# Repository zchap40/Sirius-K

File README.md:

# Sirius-K
Transparent overdrive guitar effects pedal

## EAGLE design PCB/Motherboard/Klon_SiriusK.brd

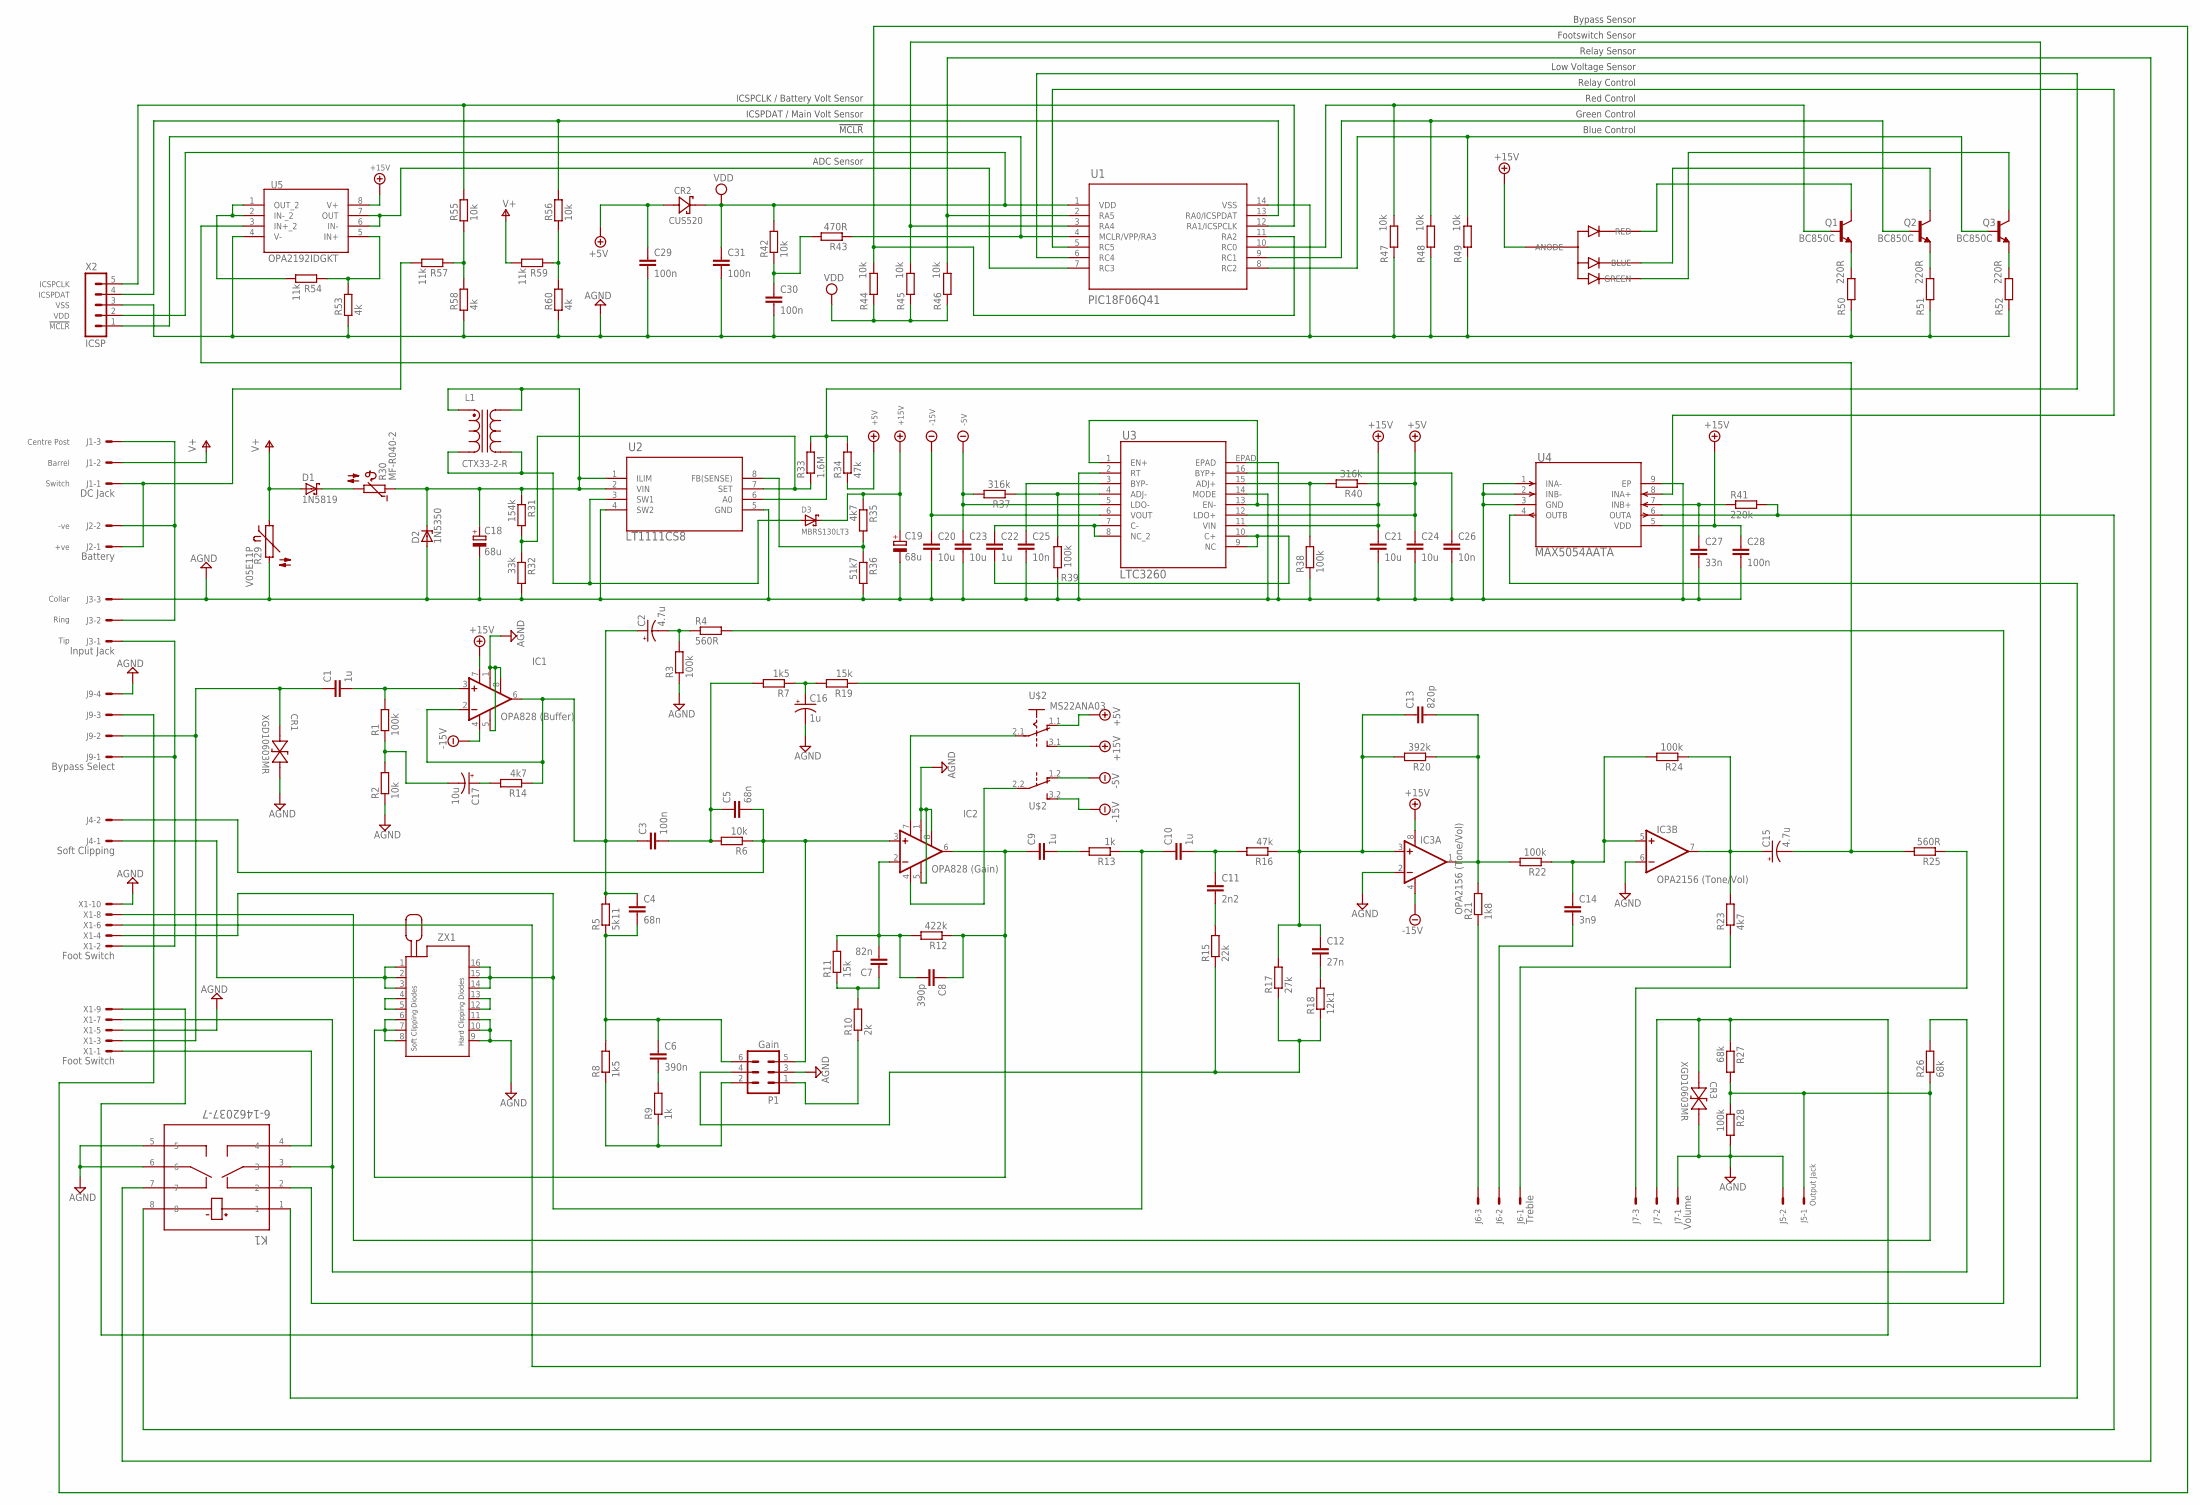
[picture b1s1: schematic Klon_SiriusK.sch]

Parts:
C1, C9, C10: 1u; C225-108X268
C2, C15: 4.7u; E15-5
C3: 100n; C102-064X133
C4, C5: 68n; C102-054X133
C6: 390n; C102-064X133
C7: 82n; C102-064X133
C8: 390p; C050-045X075
C11: 2n2; C075-042X103
C12: 27n; C102-064X133
C13: 820p; C050-050X075
C14: 3n9; C102-064X133
C16: 1u; E2,5RE
C17: 10u; E5R
C18, C19: 68u; SANYO-OSCON_SMD_F12
C20, C21, C23, C24: 10u; C1206K
C22: 1u; C0805K
C25, C26: 10n; C0603K
C27: 33n; C0603K
C28, C29, C30, C31: 100n; C0603K
CR1, CR3: XGD10603MR; ZDO_XGD10603NR_LTF-M
CR2: CUS520; USC_TOS-M
D1: 1N5819; DO41-7.6
D2: 1N5350; C1702-15
D3: MBRS130LT3; SMB
IC1: OPA828 (Buffer); DIL08
IC2: OPA828 (Gain); DIL08
IC3: OPA2156 (Tone/Vol); DIL08
J1: DC Jack; 6410-03
J2: Battery; 6410-02
J3: Input Jack; 6410-03
J4: Soft Clipping; 6410-02
J5: Output Jack; 6410-02
J6: Treble; 6410-03
J7: Volume; 6410-03
J9: Bypass Select; 6410-04
K1: 6-1462037-7; RELAY8_SMTGUL_TEC
L1: CTX33-2-R; INDM889889X597N
LED: WP154A4SEJ3VBDZGW/CA; LED5MMRGB
P1: Gain; 87831-06
Q1, Q2, Q3: BC850C; SOT23-BEC
R1, R3, R22, R24, R28: 100k; 0309/12
R2, R6: 10k; 0309/12
R4, R25: 560R; 0309/12
R5: 5k11; 0309/12
R7, R8: 1k5; 0309/12
R9, R13: 1k; 0309/12
R10: 2k; 0309/12
R11, R19: 15k; 0309/12
R12: 422k; 0309/12
R14, R23: 4k7; 0309/12
R15: 22k; 0309/12
R16: 47k; 0309/12
R17: 27k; 0309/12
R18: 12k1; 0309/12
R20: 392k; 0309/12
R21: 1k8; 0309/12
R26, R27: 68k; 0309/12
R29: V05E11P; S05K11
R30: MF-R040-2; B57164
R31: 154k; R0603
R32: 33k; R0603
R33: 1.6M; R0603
R34: 47k; R0603
R35: 4k7; R0603
R36: 51k7; R0603
R37, R40: 316k; R0603
R38, R39: 100k; R0603
R41: 220k; R0603
R42, R44, R45, R46, R47, R48, R49, R55, R56: 10k; R0603
R43: 470R; R0603
R50, R51, R52: 220R; R0603
R53, R58, R60: 4k; R0603
R54, R57, R59: 11k; R0603
U1: PIC18F06Q41; TSSOP14_ST_MCH-M
U2: LT1111CS8; SO-8_S_LIT-M
U3: LTC3260; MSOP-16_MSE_LIT-M
U4: MAX5054AATA; 21-0137_T833+2_MXM-M
U5: OPA2192IDGKT; DGK0008A_N_TEX
U$2: MS22ANA03
X1: Foot Switch; 87758-1016
X2: ICSP; MA05-1
ZX1: 216-3340-00-0602J

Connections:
+5V: C24.1, C29.1, CR2.2 (ANODE), R34.1, R40.1, U3.12 (LDO+), U$2.1.1 (O)
+15V: C19.+, C21.1, C28.1, D3.C, IC1.7 (V+), IC3.8 (V+), LED.P2 (ANODE), R35.1, U3.1 (EN+), U3.11 (VIN), U3.13 (EN-), U4.5 (VDD), U5.8 (V+), U$2.3.1 (S)
-5V: C23.1, R37.2, U3.5 (LDO-), U$2.1.2 (O)
-15V: C20.1, IC1.4 (V-), IC3.4 (V-), U3.6 (VOUT), U$2.3.2 (S)
AGND: C16.-, C18.-, C19.-, C20.2, C21.2, C23.2, C24.2, C25.2, C26.2, C27.2, C28.2, C29.2, C30.2, C31.2, CR1.1 (11), CR3.1 (11), D2.A, IC1.1 (TRIM1), IC1.5 (TRIM2), IC1.8 (NC), IC2.1 (TRIM1), IC2.5 (TRIM2), IC2.8 (NC), IC3.2 (-IN), IC3.6 (-IN), J3.3, J5.2, J7.1, J9.4, K1.5, K1.6, P1.3, R2.1, R3.1, R28.2, R29.2, R32.2, R36.2, R38.1, R39.1, R47.1, R48.1, R49.1, R50.1, R51.1, R52.1, R53.1, R58.1, R60.1, U1.14 (VSS), U2.4 (SW2), U2.5 (GND), U3.2 (RT), U3.14 (MODE), U3.EPAD, U4.1 (INA-), U4.2 (INB-), U4.3 (GND), U4.9 (EP), U5.4 (V-), X1.5, X1.10, X2.3, ZX1.9, ZX1.10, ZX1.11
unnamed: J1.1, J2.1, R57.2
unnamed: J1.3, J2.2, J3.2
unnamed: C1.1, CR1.2 (12), J9.2, X1.3
unnamed: C1.2, IC1.3 (+IN), R1.2
unnamed: C17.-, R1.1, R2.2
unnamed: C2.+, C3.1, C4.1, IC1.2 (-IN), IC1.6 (OUT), R5.2, R14.1
unnamed: D1.C, R30.2
unnamed: C17.+, R14.2
unnamed: R37.1, R39.2, U3.4 (ADJ-)
unnamed: C13.2, IC3.1 (OUT), R20.1, R21.2, R22.2
unnamed: C4.2, C6.1, P1.6, R5.1, R8.2
unnamed: C2.-, R3.2, R4.1
unnamed: C3.2, C5.1, R6.2, R7.2
unnamed: C5.2, IC2.3 (+IN), J4.2, P1.5, R6.1
unnamed: C16.+, R7.1, R19.2
unnamed: C6.2, R9.2
unnamed: P1.2, R8.1, R9.1
unnamed: C14.1, IC3.5 (+IN), R22.1, R24.2
unnamed: IC2.7 (V+), U$2.2.1
unnamed: IC2.4 (V-), U$2.2.2
unnamed: P1.4, R15.1, R17.1, R18.1
unnamed: ZX1.4, ZX1.5
unnamed: ZX1.12, ZX1.13
unnamed: C10.1, R13.1, X1.4, ZX1.14, ZX1.15, ZX1.16
unnamed: J6.3, R21.1
unnamed: C14.2, J6.2
unnamed: J4.1, ZX1.1, ZX1.2, ZX1.3
unnamed: C15.+, IC3.7 (OUT), R23.2, R24.1
unnamed: P1.1, R10.1
unnamed: C7.1, R10.2, R11.1
unnamed: C7.2, C8.2, IC2.2 (-IN), R11.2, R12.2
unnamed: J6.1, R23.1
unnamed: C8.1, C9.1, IC2.6 (OUT), R12.1, ZX1.6, ZX1.7, ZX1.8
unnamed: C15.-, R25.2, U5.3 (IN+_2)
unnamed: J7.3, R25.1
unnamed: J3.1, J9.1, X1.2
unnamed: C9.2, R13.2
unnamed: J5.1, R26.1, R27.2, R28.1, X1.8
unnamed: C10.2, C11.1, R16.2
unnamed: C11.2, R15.2
unnamed: C12.1, C13.1, IC3.3 (+IN), R16.1, R17.2, R19.1, R20.2
unnamed: C12.2, R18.2
unnamed: CR3.2 (12), J7.2, R27.1, X1.9
unnamed: K1.4, X1.1
unnamed: K1.2, R4.2
unnamed: K1.3, R26.2, X1.7
unnamed: K1.1, U4.4 (OUTB)
unnamed: K1.8, R41.2, U4.6 (OUTA)
unnamed: Q3.E, R52.2
unnamed: Q2.E, R51.2
unnamed: J9.3, R44.2, U1.11 (RA2)
unnamed: R31.2, R32.1, R33.1, U2.7 (SET)
unnamed: Q1.E, R50.2
unnamed: C18.+, D2.C, L1.1, L1.4, R30.1, R31.1, U2.1 (ILIM), U2.2 (VIN)
unnamed: C22.1, U3.7 (C-), U3.8 (NC_2)
unnamed: D3.A, L1.2, L1.3, U2.3 (SW1)
unnamed: R35.2, R36.1, U2.8 (FB(SENSE))
unnamed: R38.2, R40.2, U3.15 (ADJ+)
unnamed: C27.1, R41.1, U4.7 (INB+)
unnamed: R54.2, U5.1 (OUT_2), U5.2 (IN-_2)
unnamed: R56.2, U1.13 (RA0/ICSPDAT), X2.4
unnamed: C26.1, U3.16 (BYP+)
unnamed: R55.2, U1.12 (RA1/ICSPCLK), X2.5
unnamed: C25.1, U3.3 (BYP-)
unnamed: R43.1, U1.4 (MCLR/VPP/RA3), X2.1
unnamed: K1.7, R46.2, U1.2 (RA5)
unnamed: R45.2, U1.3 (RA4), X1.6
unnamed: C30.1, R42.1, R43.2
unnamed: LED.P1 (RED), Q1.C
unnamed: U1.5 (RC5), U4.8 (INA+)
unnamed: Q1.B, R47.2, U1.10 (RC0)
unnamed: Q2.B, R48.2, U1.9 (RC1)
unnamed: Q3.B, R49.2, U1.8 (RC2)
unnamed: R33.2, R34.2, U1.6 (RC4), U2.6 (A0)
unnamed: LED.P3 (BLUE), Q2.C
unnamed: LED.P4 (GREEN), Q3.C
unnamed: U1.7 (RC3), U5.6 (IN-), U5.7 (OUT)
unnamed: R56.1, R59.1, R60.2
unnamed: R53.2, R54.1, U5.5 (IN+)
unnamed: R55.1, R57.1, R58.2
unnamed: C22.2, U3.9 (NC), U3.10 (C+)
V+: D1.A, J1.2, R29.1, R59.2
VDD: C31.1, CR2.1 (CATHODE), R42.2, R44.1, R45.1, R46.1, U1.1 (VDD), X2.2

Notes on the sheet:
Switch
Centre Post
Barrel
Tip
Ring
Collar
+ve
-ve
!MCLR!
VDD
VSS
ICSPDAT
ICSPCLK
Bypass Sensor
Footswitch Sensor
Relay Sensor
Low Voltage Sensor
Relay Control
Red Control
Green Control
Blue Control
Soft Clipping Diodes
Hard Clipping Diodes
ADC Sensor
ICSPCLK / Battery Volt Sensor
ICSPDAT / Main Volt Sensor

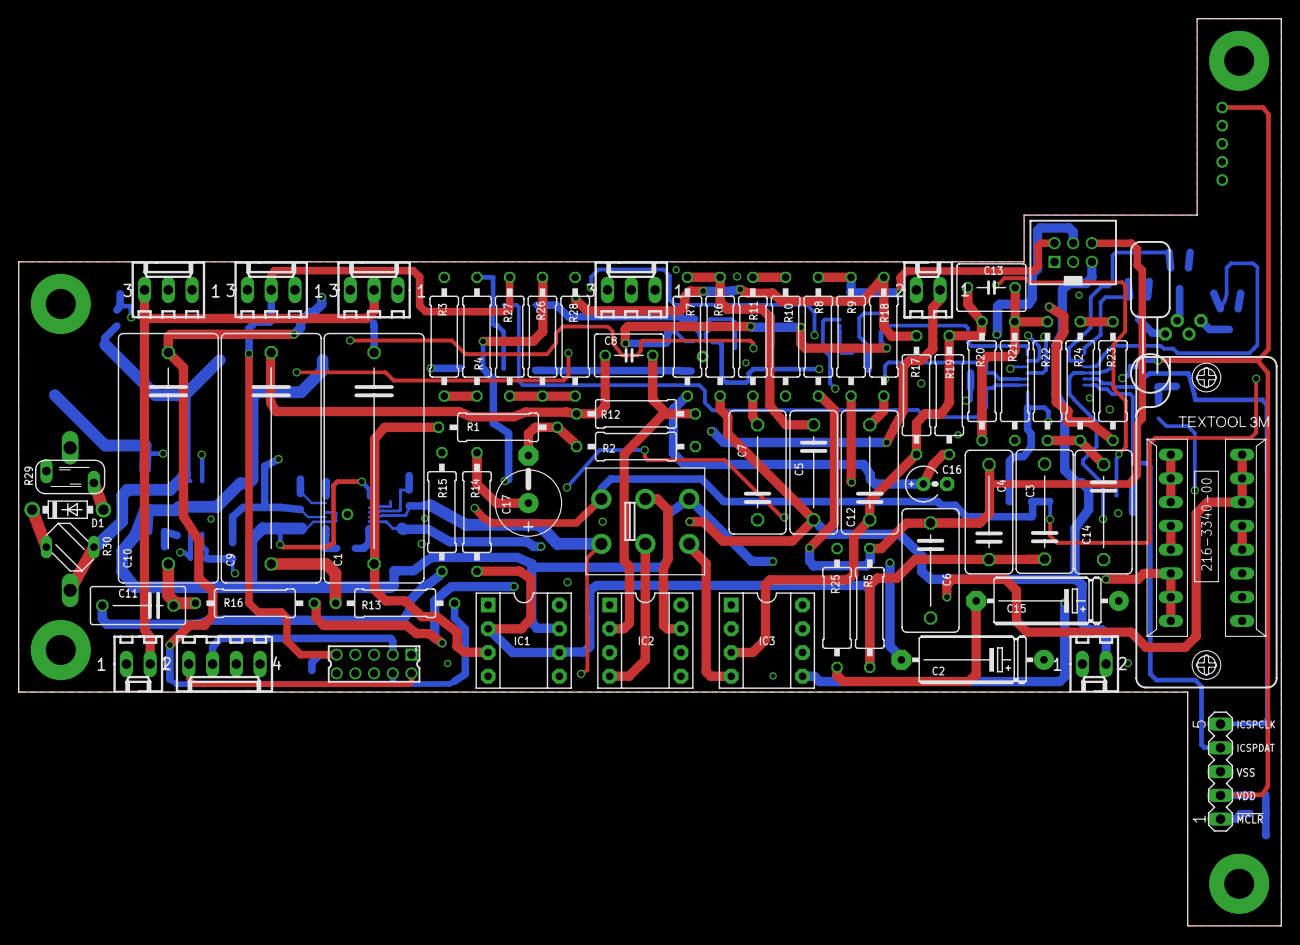
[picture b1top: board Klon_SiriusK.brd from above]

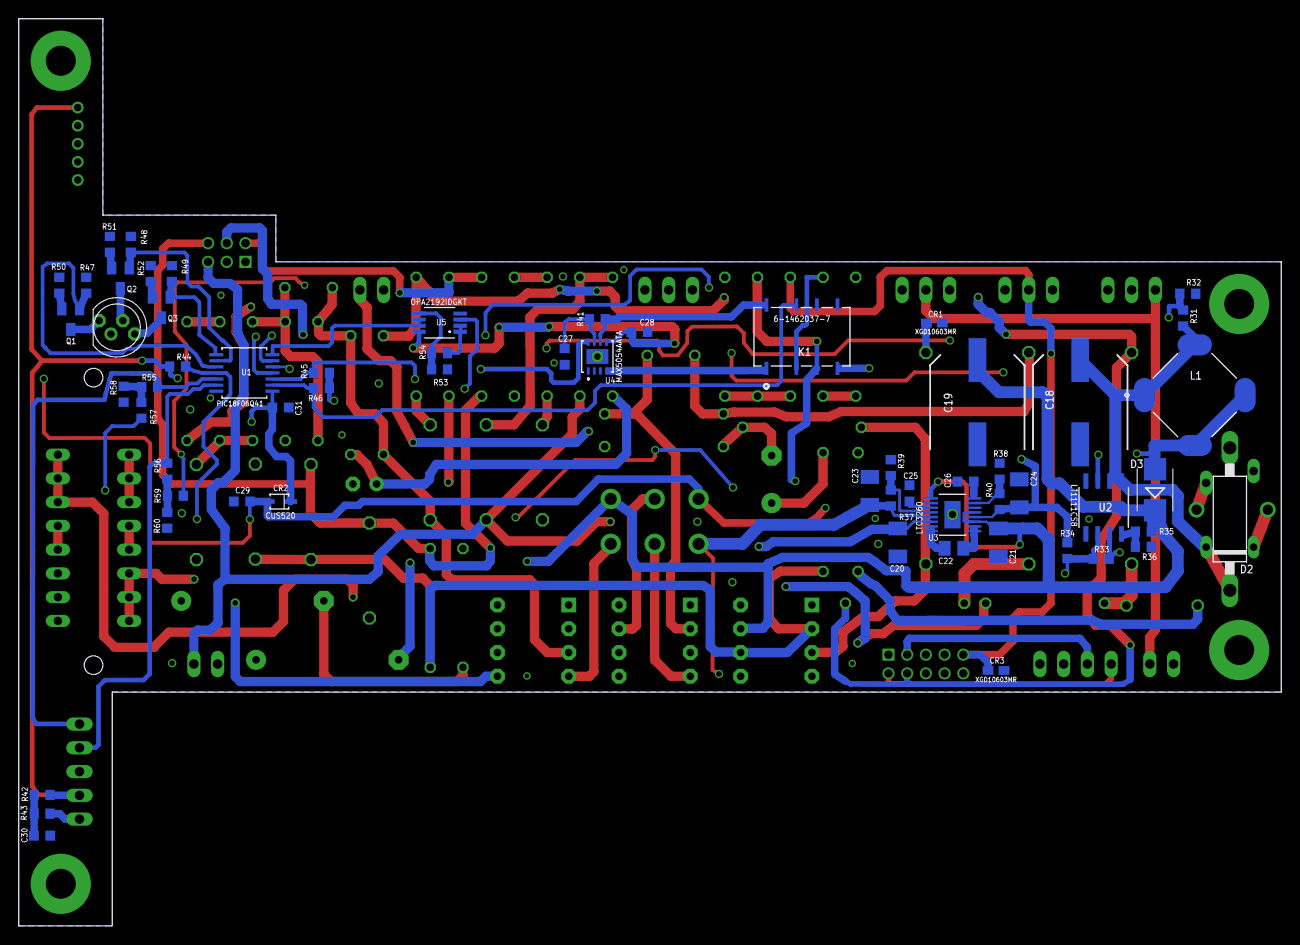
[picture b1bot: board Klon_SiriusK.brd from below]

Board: 4 copper layers, 135.0 x 97.0 mm, 124 parts (60 on the bottom side), 88 nets.

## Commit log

2022-09-29 Uploading to repository

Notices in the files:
parts and their libraries:
con-molex-milli-grid: Copyright (C) 2010, Bob Starr
COPYRIGHT: Copyright (C) 2018 Accelerated Designs. All rights reserved
COPYRIGHT: Copyright (C) 2016 Accelerated Designs. All rights reserved
